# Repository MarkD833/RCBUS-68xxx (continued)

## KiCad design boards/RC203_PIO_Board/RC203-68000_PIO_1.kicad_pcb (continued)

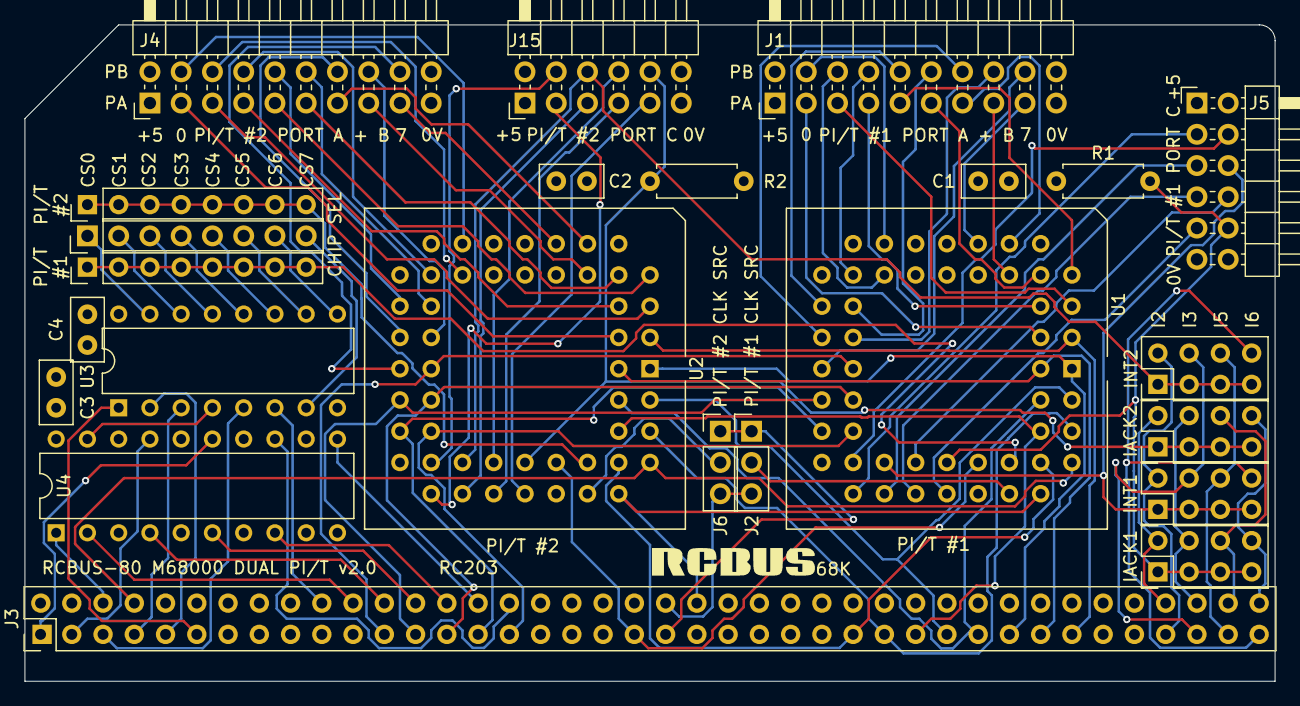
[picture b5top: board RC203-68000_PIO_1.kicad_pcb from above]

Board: 4 copper layers, 101.6 x 53.3 mm, 24 parts (0 on the bottom side), 103 nets.

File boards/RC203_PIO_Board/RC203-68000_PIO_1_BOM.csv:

Reference,Value,Footprint,Qty,Description
"C1,C2,C3,C4",100n,Capacitor_THT:C_Disc_D5.0mm_W2.5mm_P2.50mm,4,Unpolarized ceramic capacitor
"J1,J4,J5",Conn_02x08_Odd_Even,MyLibrary2023:PinHeader_2x08_P2.54mm_Vertical,3,"Generic connector, double row, 02x08, right angle"
"J2,J6",Conn_01x03,Connector_PinHeader_2.54mm:PinHeader_1x03_P2.54mm_Vertical,2,"Generic connector, single row, 01x03"
J3,RCBus_80PIN_68000,MyLibrary2023:RCBus_80p_Medium,1,"Generic connector, double row, 02x40, right angle"
"J7,J12,J13",Conn_01x08,Connector_PinHeader_2.54mm:PinHeader_1x08_P2.54mm_Vertical,3,"Generic connector, single row, 01x08"
"J8,J9,J10,J11",Conn_02x04_Odd_Even,MyLibrary2023:PinHeader_2x04_P2.54mm_Vertical,4,"Generic connector, double row, 02x04"
J14,Conn_02x03_Odd_Even,Connector_PinSocket_2.54mm:PinSocket_2x03_P2.54mm_Vertical,1,"Generic connector, double row, 02x03, right angle"
J15,Conn_01x06,Connector_PinSocket_2.54mm:PinSocket_1x06_P2.54mm_Vertical,1,"Generic connector, single row, 01x06, right angle"
"U1,U2",MC68230,MyLibrary2023:DIP-48_W15.24mm_Socket,2,Parallel Interface / Timer
U3,74LS138,Package_DIP:DIP-16_W7.62mm_Socket,1,Decoder 3 to 8 active low outputs
U4,74LS688,MyLibrary2023:DIP-20_W7.62mm_Socket,1,8-bit magnitude comparator

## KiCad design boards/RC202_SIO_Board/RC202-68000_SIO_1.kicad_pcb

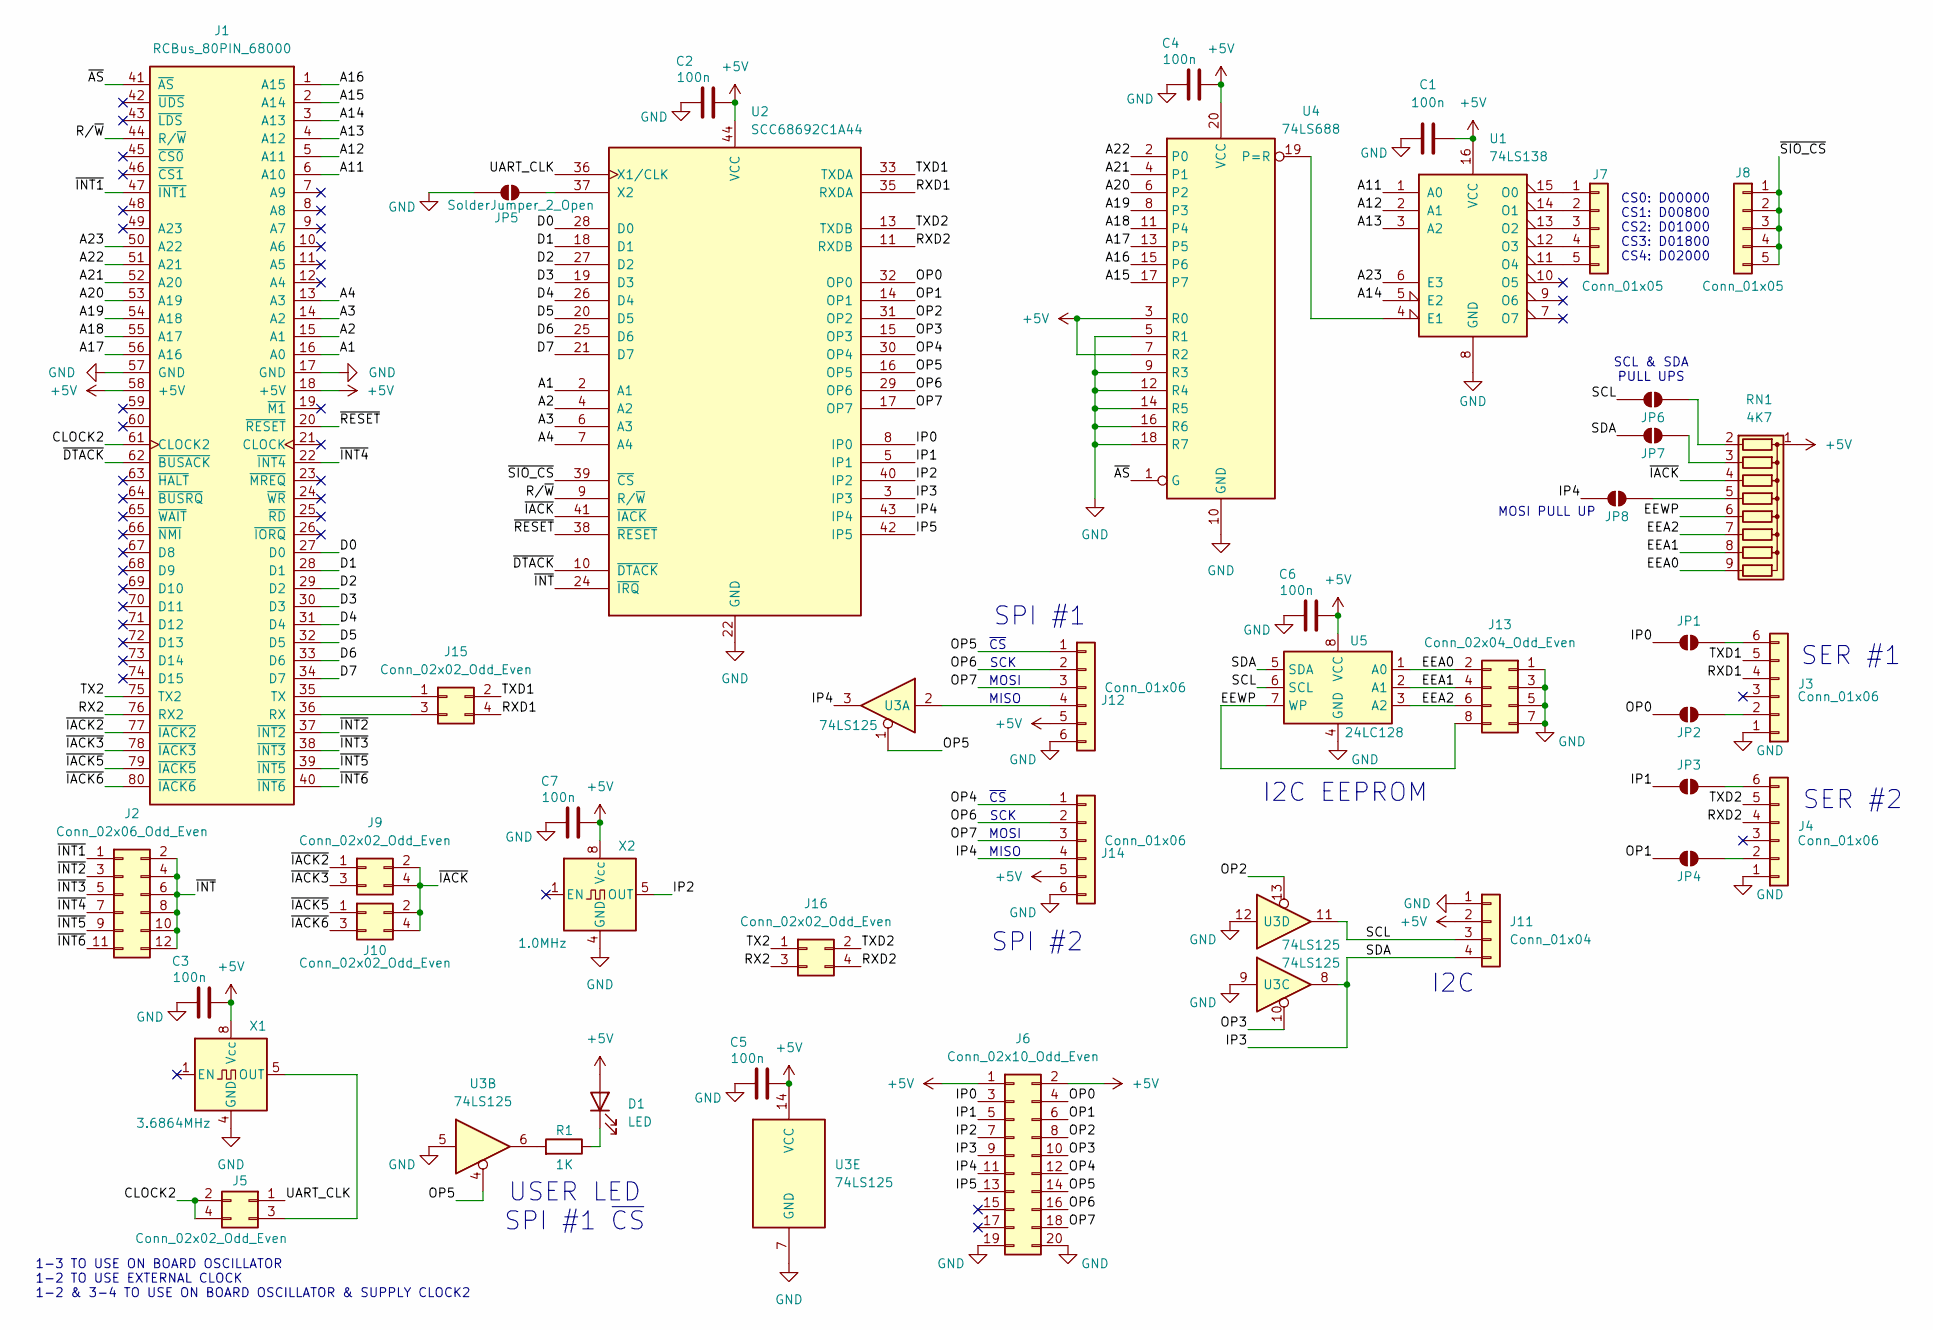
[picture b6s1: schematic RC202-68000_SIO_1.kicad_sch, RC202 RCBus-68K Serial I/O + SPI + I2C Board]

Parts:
C1, C2, C3, C4, C5, C6, C7: 100n; C_Disc_D5.0mm_W2.5mm_P2.50mm
D1: LED; LED_D3.0mm
J1: RCBus_80PIN_68000; RCBus_80p_Medium
J2: Conn_02x06_Odd_Even; PinHeader_2x06_P2.54mm_Vertical
J3, J4, J12, J14: Conn_01x06; PinSocket_1x06_P2.54mm_Horizontal
J5, J9, J10, J15, J16: Conn_02x02_Odd_Even; PinHeader_2x02_P2.54mm_Vertical
J6: Conn_02x10_Odd_Even; PinHeader_2x10_P2.54mm_Horizontal
J7, J8: Conn_01x05; PinHeader_1x05_P2.54mm_Vertical
J11: Conn_01x04; PinHeader_1x04_P2.54mm_Horizontal
J13: Conn_02x04_Odd_Even; PinHeader_2x04_P2.54mm_Vertical
JP1, JP2, JP3, JP4, JP6, JP7, JP8: SolderJumper; SolderJumper-2_P1.3mm_Open_Pad1.0x1.5mm
JP5: SolderJumper_2_Open; SolderJumper-2_P1.3mm_Open_Pad1.0x1.5mm
R1: 1K; R_Axial_DIN0207_L6.3mm_D2.5mm_P7.62mm_Horizontal
RN1: 4K7; R_Array_SIP9
U1: 74LS138; DIP-16_W7.62mm
U2: SCC68692C1A44; PLCC-44_THT-Socket
U3: 74LS125; DIP-14_W7.62mm
U4: 74LS688; DIP-20_W7.62mm
U5: 24LC128; DIP-8_W7.62mm
X1: 3.6864MHz; Oscillator_DIP-8
X2: 1.0MHz; Oscillator_DIP-8

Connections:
+5V: C1.2, C2.2, C3.2, C4.2, C5.2, C6.2, C7.2, D1.2 (A), J1.18 (+5V), J1.58 (+5V), J6.1, J6.2, J11.2, J12.5, J14.5, RN1.1 (common), U1.16 (VCC), U2.44 (VCC), U3.14 (VCC), U4.3 (R0), U4.7 (R2), U4.20 (VCC), U5.8 (VCC), X1.8 (Vcc), X2.8 (Vcc)
/A1: J1.16 (A0), U2.2 (A1)
/A2: J1.15 (A1), U2.4 (A2)
/A3: J1.14 (A2), U2.6 (A3)
/A4: J1.13 (A3), U2.7 (A4)
/A11: J1.6 (A10), U1.1 (A0)
/A12: J1.5 (A11), U1.2 (A1)
/A13: J1.4 (A12), U1.3 (A2)
/A14: J1.3 (A13), U1.5 (E2)
/A15: J1.2 (A14), U4.17 (P7)
/A16: J1.1 (A15), U4.15 (P6)
/A17: J1.56 (A16), U4.13 (P5)
/A18: J1.55 (A17), U4.11 (P4)
/A19: J1.54 (A18), U4.8 (P3)
/A20: J1.53 (A19), U4.6 (P2)
/A21: J1.52 (A20), U4.4 (P1)
/A22: J1.51 (A21), U4.2 (P0)
/A23: J1.50 (A22), U1.6 (E3)
/CLOCK2: J1.61 (CLOCK2), J5.2, J5.4
/D0: J1.27 (D0), U2.28 (D0)
/D1: J1.28 (D1), U2.18 (D1)
/D2: J1.29 (D2), U2.27 (D2)
/D3: J1.30 (D3), U2.19 (D3)
/D4: J1.31 (D4), U2.26 (D4)
/D5: J1.32 (D5), U2.20 (D5)
/D6: J1.33 (D6), U2.25 (D6)
/D7: J1.34 (D7), U2.21 (D7)
/EEA0: J13.2, RN1.9 (R8), U5.1 (A0)
/EEA1: J13.4, RN1.8 (R7), U5.2 (A1)
/EEA2: J13.6, RN1.7 (R6), U5.3 (A2)
/EEWP: J13.8, RN1.6 (R5), U5.7 (WP)
/IP0: J6.3, JP1.1 (A), U2.8 (IP0)
/IP1: J6.5, JP3.1 (A), U2.5 (IP1)
/IP2: J6.7, U2.40 (IP2), X2.5 (OUT)
/IP3: J6.9, J11.4, JP7.1 (A), U2.3 (IP3), U3.8, U5.5 (SDA)
/IP4: J6.11, J14.4, JP8.1 (A), U2.43 (IP4), U3.3
/IP5: J6.13, U2.42 (IP5)
/OP0: J6.4, JP2.1 (A), U2.32 (OP0)
/OP1: J6.6, JP4.1 (A), U2.14 (OP1)
/OP2: J6.8, U2.31 (OP2), U3.13
/OP3: J6.10, U2.15 (OP3), U3.10
/OP4: J6.12, J14.1, U2.30 (OP4)
/OP5: J6.14, J12.1, U2.16 (OP5), U3.1, U3.4
/OP6: J6.16, J12.2, J14.2, U2.29 (OP6)
/OP7: J6.18, J12.3, J14.3, U2.17 (OP7)
/RX2: J1.76 (RX2), J16.3
/RXD1: J3.4, J15.4, U2.35 (RXDA)
/RXD2: J4.4, J16.4, U2.11 (RXDB)
/R/~W: J1.44 (R/~W), U2.9 (R/~W)
/SCL: J11.3, JP6.1 (A), U3.11, U5.6 (SCL)
/TX2: J1.75 (TX2), J16.1
/TXD1: J3.5, J15.2, U2.33 (TXDA)
/TXD2: J4.5, J16.2, U2.13 (TXDB)
/UART_CLK: J5.1, U2.36 (X1/CLK)
/~AS: J1.41 (~AS), U4.1 (G)
/~DTACK: J1.62 (~BUSACK), U2.10 (~DTACK)
/~IACK2: J1.77 (~IACK2), J9.1
/~IACK3: J1.78 (~IACK3), J9.3
/~IACK5: J1.79 (~IACK5), J10.1
/~IACK6: J1.80 (~IACK6), J10.3
/~IACK: J9.2, J9.4, J10.2, J10.4, RN1.4 (R3), U2.41 (~IACK)
/~INT1: J1.47 (~INT1), J2.1
/~INT2: J1.37 (~INT2), J2.3
/~INT3: J1.38 (~INT3), J2.5
/~INT4: J1.22 (~INT4), J2.7
/~INT5: J1.39 (~INT5), J2.9
/~INT6: J1.40 (~INT6), J2.11
/~INT: J2.2, J2.4, J2.6, J2.8, J2.10, J2.12, U2.24 (~IRQ)
/~RESET: J1.20 (~RESET), U2.38 (~RESET)
/~SIO_CS: J8.1, J8.2, J8.3, J8.4, J8.5, U2.39 (~CS)
GND: C1.1, C2.1, C3.1, C4.1, C5.1, C6.1, C7.1, J1.17 (GND), J1.57 (GND), J3.1, J4.1, J6.19, J6.20, J11.1, J12.6, J13.1, J13.3, J13.5, J13.7, J14.6, JP5.2 (B), U1.8 (GND), U2.22 (GND), U3.5, U3.7 (GND), U3.9, U3.12, U4.5 (R1), U4.9 (R3), U4.10 (GND), U4.12 (R4), U4.14 (R5), U4.16 (R6), U4.18 (R7), U5.4 (GND), X1.4 (GND), X2.4 (GND)
unnamed: D1.1 (K), R1.1
unnamed: J1.36 (RX), J15.3
unnamed: J1.35 (TX), J15.1
unnamed: J3.2, JP2.2 (B)
unnamed: J3.6, JP1.2 (B)
unnamed: J4.2, JP4.2 (B)
unnamed: J4.6, JP3.2 (B)
unnamed: J5.3, X1.5 (OUT)
unnamed: J7.1, U1.15 (O0)
unnamed: J7.2, U1.14 (O1)
unnamed: J7.3, U1.13 (O2)
unnamed: J7.4, U1.12 (O3)
unnamed: J7.5, U1.11 (O4)
unnamed: J12.4, U3.2
unnamed: JP5.1 (A), U2.37 (X2)
unnamed: JP6.2 (B), RN1.2 (R1)
unnamed: JP7.2 (B), RN1.3 (R2)
unnamed: JP8.2 (B), RN1.5 (R4)
unnamed: R1.2, U3.6
unnamed: U1.4 (E1), U4.19 (P=R)

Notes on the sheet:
I2C EEPROM
SCK
SCL & SDA PULL UPS
~{CS}
MOSI PULL UP
MISO
MOSI
I2C
CS0: D00000 CS1: D00800 CS2: D01000 CS3: D01800 CS4: D02000
SER #1
SER #2
SPI #1
1-3 TO USE ON BOARD OSCILLATOR 1-2 TO USE EXTERNAL CLOCK 1-2 & 3-4 TO USE ON BOARD OSCILLATOR & SUPPLY CLOCK2
USER LED SPI #1 ~{CS}
SPI #2

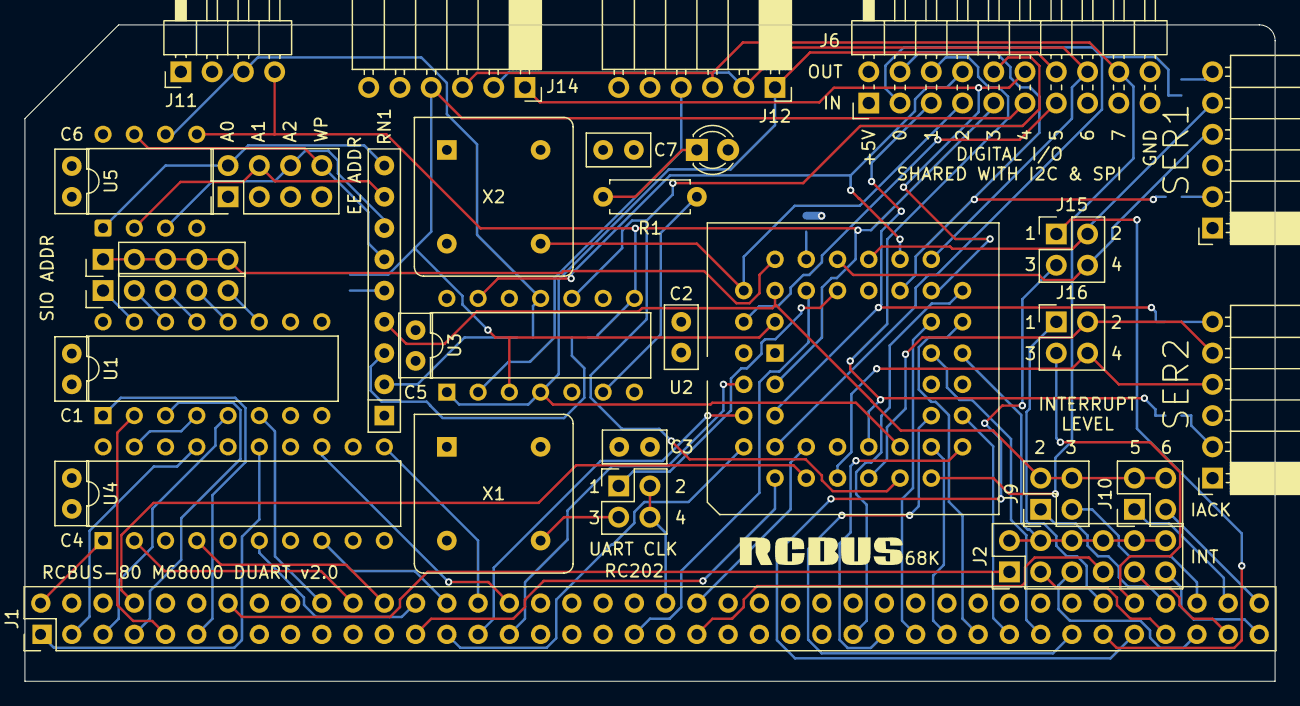
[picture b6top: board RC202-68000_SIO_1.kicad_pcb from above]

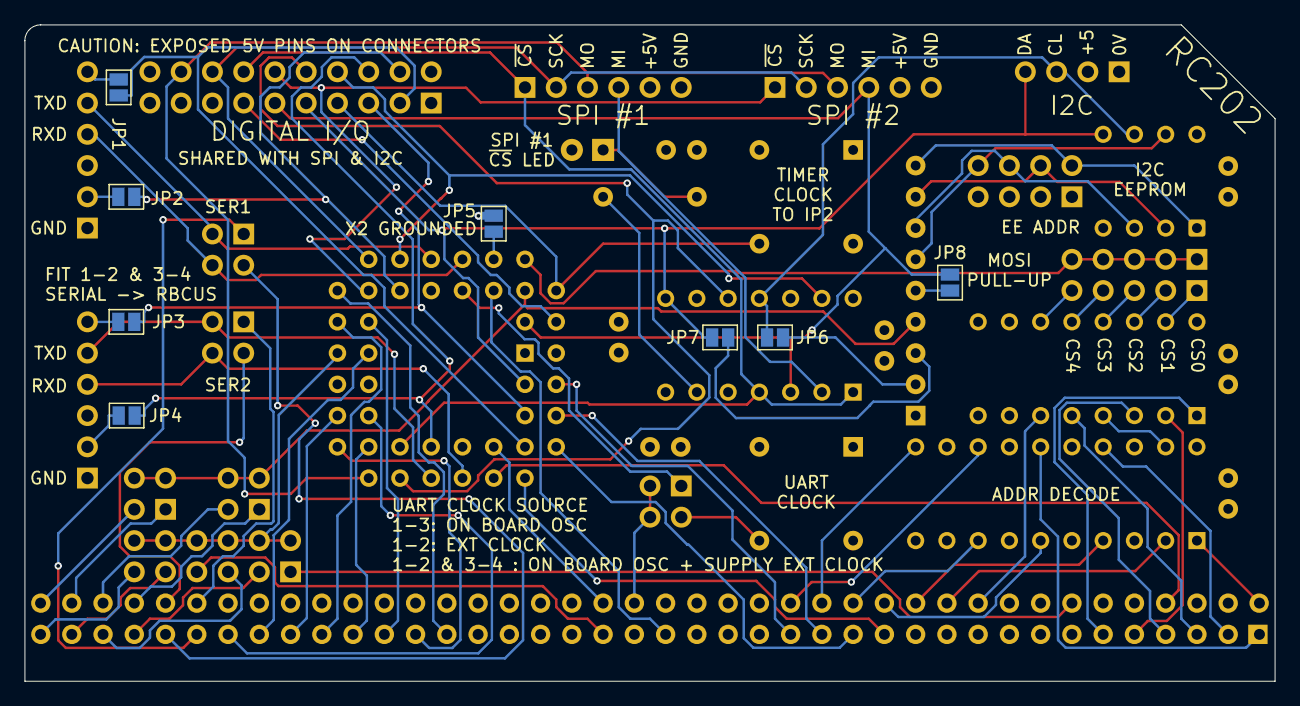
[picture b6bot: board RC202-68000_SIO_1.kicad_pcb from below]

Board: 4 copper layers, 101.6 x 53.3 mm, 41 parts (8 on the bottom side), 91 nets.

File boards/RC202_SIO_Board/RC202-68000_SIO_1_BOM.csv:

Reference,Value,Qty,Description
"C1,C2,C3,C4,C5,C6,C7",100n,7,Unpolarized ceramic capacitor
D1,LED,1,Light emitting diode
J1,RCBus_80PIN_68000,1,"Generic connector, double row, 02x40, right angle"
J2,Conn_02x06_Odd_Even,1,"Generic connector, double row, 02x06"
"J3,J4,J12,J14",Conn_01x06,4,"Generic connector, single row, 01x06, right angle"
"J5,J9,J10,J15,J16",Conn_02x02_Odd_Even,5,"Generic connector, double row, 02x02"
J6,Conn_02x10_Odd_Even,1,"Generic connector, double row, 02x10"
"J7,J8",Conn_01x05,2,"Generic connector, single row, 01x05"
J11,Conn_01x04,1,"Generic connector, single row, 01x04"
J13,Conn_02x04_Odd_Even,1,"Generic connector, double row, 02x04"
"JP1,JP2,JP3,JP4,JP6,JP7,JP8",SolderJumper,7,"Solder Jumper, 2-pole, open"
R1,1K,1,Resistor
RN1,4K7,1,"8 resistor network, star topology, bussed resistors, small symbol"
U1,74LS138,1,Decoder 3 to 8 active low outputs
U2,SCC68692C1A44,1,DUART + 8 Outputs & 6 Inputs
U3,74LS125,1,Quad buffer 3-State outputs
U4,74LS688,1,8-bit magnitude comparator
U5,24LC128,1,"I2C Serial EEPROM, 128Kb, DIP-8"
X1,3.6864MHz,1,"Crystal Clock Oscillator, DIP8-style metal package"
X2,1.0MHz,1,"Crystal Clock Oscillator, DIP8-style metal package"

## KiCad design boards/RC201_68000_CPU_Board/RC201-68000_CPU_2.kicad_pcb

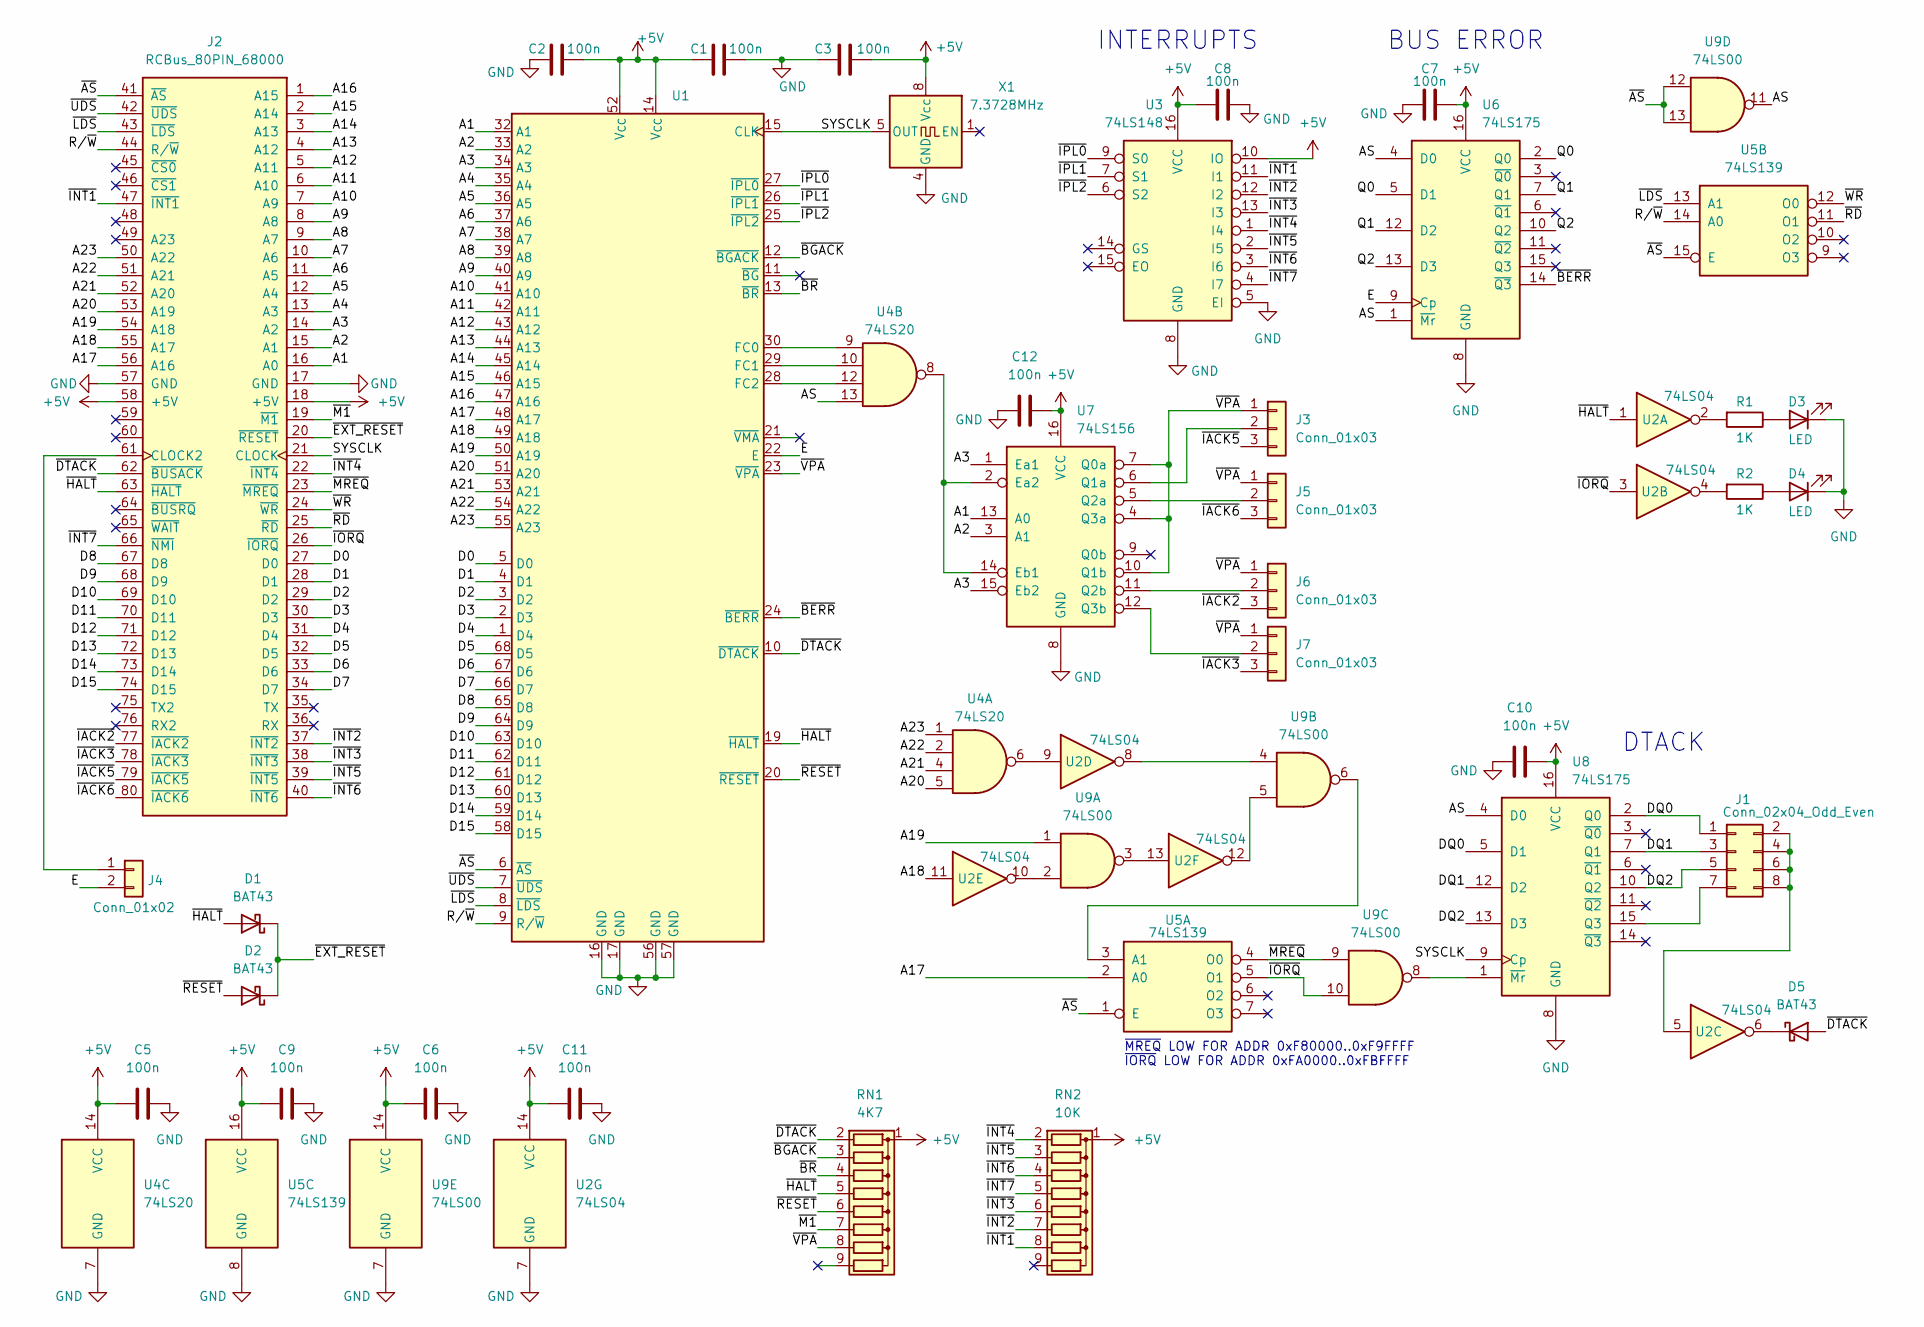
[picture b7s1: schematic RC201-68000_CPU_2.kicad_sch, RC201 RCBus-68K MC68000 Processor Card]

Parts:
C1, C2, C3, C5, C6, C7, C8, C9, C10, C11, C12: 100n; C_Disc_D5.0mm_W2.5mm_P2.50mm
D1, D2, D5: BAT43; D_DO-35_SOD27_P7.62mm_Horizontal
D3, D4: LED; LED_D3.0mm
J1: Conn_02x04_Odd_Even; PinHeader_2x04_P2.54mm_Vertical
J2: RCBus_80PIN_68000; RCBus_80p_Medium
J3, J5, J6, J7: Conn_01x03; PinHeader_1x03_P2.54mm_Vertical
J4: Conn_01x02; PinHeader_1x02_P2.54mm_Vertical
R1, R2: 1K; R_Axial_DIN0207_L6.3mm_D2.5mm_P7.62mm_Horizontal
RN1: 4K7; R_Array_SIP9
RN2: 10K; R_Array_SIP9
U1: PLCC-68_THT-Socket
U2: 74LS04; DIP-14_W7.62mm
U3: 74LS148; DIP-16_W7.62mm
U4: 74LS20; DIP-14_W7.62mm
U5: 74LS139; DIP-16_W7.62mm
U6, U8: 74LS175; DIP-16_W7.62mm
U7: 74LS156; DIP-16_W7.62mm
U9: 74LS00; DIP-14_W7.62mm
X1: 7.3728MHz; Oscillator_DIP-8

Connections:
+5V: C1.1, C2.2, C3.2, C5.1, C6.1, C7.2, C8.1, C9.1, C10.2, C11.1, C12.2, J2.18 (+5V), J2.58 (+5V), RN1.1 (common), RN2.1 (common), U1.14 (V_{CC}), U1.52 (V_{CC}), U2.14 (VCC), U3.10 (IO), U3.16 (VCC), U4.14 (VCC), U5.16 (VCC), U6.16 (VCC), U7.16 (VCC), U8.16 (VCC), U9.14 (VCC), X1.8 (Vcc)
/A1: J2.16 (A0), U1.32 (A1), U7.13 (A0)
/A2: J2.15 (A1), U1.33 (A2), U7.3 (A1)
/A3: J2.14 (A2), U1.34 (A3), U7.1 (Ea1), U7.15 (Eb2)
/A4: J2.13 (A3), U1.35 (A4)
/A5: J2.12 (A4), U1.36 (A5)
/A6: J2.11 (A5), U1.37 (A6)
/A7: J2.10 (A6), U1.38 (A7)
/A8: J2.9 (A7), U1.39 (A8)
/A9: J2.8 (A8), U1.40 (A9)
/A10: J2.7 (A9), U1.41 (A10)
/A11: J2.6 (A10), U1.42 (A11)
/A12: J2.5 (A11), U1.43 (A12)
/A13: J2.4 (A12), U1.44 (A13)
/A14: J2.3 (A13), U1.45 (A14)
/A15: J2.2 (A14), U1.46 (A15)
/A16: J2.1 (A15), U1.47 (A16)
/A17: J2.56 (A16), U1.48 (A17), U5.2 (A0)
/A18: J2.55 (A17), U1.49 (A18), U2.11
/A19: J2.54 (A18), U1.50 (A19), U9.1
/A20: J2.53 (A19), U1.51 (A20), U4.5
/A21: J2.52 (A20), U1.53 (A21), U4.4
/A22: J2.51 (A21), U1.54 (A22), U4.2
/A23: J2.50 (A22), U1.55 (A23), U4.1
/AS: U4.13, U6.1 (~Mr), U6.4 (D0), U8.4 (D0), U9.11
/D0: J2.27 (D0), U1.5 (D0)
/D1: J2.28 (D1), U1.4 (D1)
/D2: J2.29 (D2), U1.3 (D2)
/D3: J2.30 (D3), U1.2 (D3)
/D4: J2.31 (D4), U1.1 (D4)
/D5: J2.32 (D5), U1.68 (D5)
/D6: J2.33 (D6), U1.67 (D6)
/D7: J2.34 (D7), U1.66 (D7)
/D8: J2.67 (D8), U1.65 (D8)
/D9: J2.68 (D9), U1.64 (D9)
/D10: J2.69 (D10), U1.63 (D10)
/D11: J2.70 (D11), U1.62 (D11)
/D12: J2.71 (D12), U1.61 (D12)
/D13: J2.72 (D13), U1.60 (D13)
/D14: J2.73 (D14), U1.59 (D14)
/D15: J2.74 (D15), U1.58 (D15)
/DQ0: J1.1, U8.2 (Q0), U8.5 (D1)
/DQ1: J1.3, U8.7 (Q1), U8.12 (D2)
/DQ2: J1.5, U8.10 (Q2), U8.13 (D3)
/E: J4.2, U1.22 (E), U6.9 (Cp)
/Q0: U6.2 (Q0), U6.5 (D1)
/Q1: U6.7 (Q1), U6.12 (D2)
/Q2: U6.10 (Q2), U6.13 (D3)
/R/~W: J2.44 (R/~W), U1.9 (R/~W), U5.14 (A0)
/SYSCLK: J2.21 (CLOCK), U1.15 (CLK), U8.9 (Cp), X1.5 (OUT)
/~AS: J2.41 (~AS), U1.6 (~AS), U5.1 (E), U5.15 (E), U9.12, U9.13
/~BERR: U1.24 (~BERR), U6.14 (~Q3)
/~BGACK: RN1.3 (R2), U1.12 (~BGACK)
/~BR: RN1.4 (R3), U1.13 (~BR)
/~DTACK: D5.2 (A), J2.62 (~BUSACK), RN1.2 (R1), U1.10 (~DTACK)
/~EXT_RESET: D1.1 (K), D2.1 (K), J2.20 (~RESET)
/~HALT: D1.2 (A), J2.63 (~HALT), RN1.5 (R4), U1.19 (~HALT), U2.1
/~IACK2: J2.77 (~IACK2), J6.3
/~IACK3: J2.78 (~IACK3), J7.3
/~IACK5: J2.79 (~IACK5), J3.3
/~IACK6: J2.80 (~IACK6), J5.3
/~INT1: J2.47 (~INT1), RN2.8 (R7), U3.11 (I1)
/~INT2: J2.37 (~INT2), RN2.7 (R6), U3.12 (I2)
/~INT3: J2.38 (~INT3), RN2.6 (R5), U3.13 (I3)
/~INT4: J2.22 (~INT4), RN2.2 (R1), U3.1 (I4)
/~INT5: J2.39 (~INT5), RN2.3 (R2), U3.2 (I5)
/~INT6: J2.40 (~INT6), RN2.4 (R3), U3.3 (I6)
/~INT7: J2.66 (~NMI), RN2.5 (R4), U3.4 (I7)
/~IORQ: J2.26 (~IORQ), U2.3, U5.5 (O1), U9.10
/~IPL0: U1.27 (~IPL0), U3.9 (S0)
/~IPL1: U1.26 (~IPL1), U3.7 (S1)
/~IPL2: U1.25 (~IPL2), U3.6 (S2)
/~LDS: J2.43 (~LDS), U1.8 (~LDS), U5.13 (A1)
/~M1: J2.19 (~M1), RN1.7 (R6)
/~MREQ: J2.23 (~MREQ), U5.4 (O0), U9.9
/~RD: J2.25 (~RD), U5.11 (O1)
/~RESET: D2.2 (A), RN1.6 (R5), U1.20 (~RESET)
/~UDS: J2.42 (~UDS), U1.7 (~UDS)
/~VPA: J3.1, J5.1, J6.1, J7.1, RN1.8 (R7), U1.23 (~VPA), U7.4 (Q3a), U7.7 (Q0a), U7.10 (Q1b)
/~WR: J2.24 (~WR), U5.12 (O0)
GND: C1.2, C2.1, C3.1, C5.2, C6.2, C7.1, C8.2, C9.2, C10.1, C11.2, C12.1, D3.1 (K), D4.1 (K), J2.17 (GND), J2.57 (GND), U1.16 (GND), U1.17 (GND), U1.56 (GND), U1.57 (GND), U2.7 (GND), U3.5 (EI), U3.8 (GND), U4.7 (GND), U5.8 (GND), U6.8 (GND), U7.8 (GND), U8.8 (GND), U9.7 (GND), X1.4 (GND)
unnamed: D3.2 (A), R1.1
unnamed: D4.2 (A), R2.1
unnamed: D5.1 (K), U2.6
unnamed: J1.2, J1.4, J1.6, J1.8, U2.5
unnamed: J1.7, U8.15 (Q3)
unnamed: J2.61 (CLOCK2), J4.1
unnamed: J3.2, U7.6 (Q1a)
unnamed: J5.2, U7.5 (Q2a)
unnamed: J6.2, U7.11 (Q2b)
unnamed: J7.2, U7.12 (Q3b)
unnamed: R1.2, U2.2
unnamed: R2.2, U2.4
unnamed: U1.30 (FC0), U4.9
unnamed: U1.29 (FC1), U4.10
unnamed: U1.28 (FC2), U4.12
unnamed: U2.8, U9.4
unnamed: U2.9, U4.6
unnamed: U2.10, U9.2
unnamed: U2.12, U9.5
unnamed: U2.13, U9.3
unnamed: U5.3 (A1), U9.6
unnamed: U4.8, U7.2 (Ea2), U7.14 (Eb1)
unnamed: U8.1 (~Mr), U9.8

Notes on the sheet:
INTERRUPTS
DTACK
~{MREQ} LOW FOR ADDR 0xF80000..0xF9FFFF ~{IORQ} LOW FOR ADDR 0xFA0000..0xFBFFFF
BUS ERROR

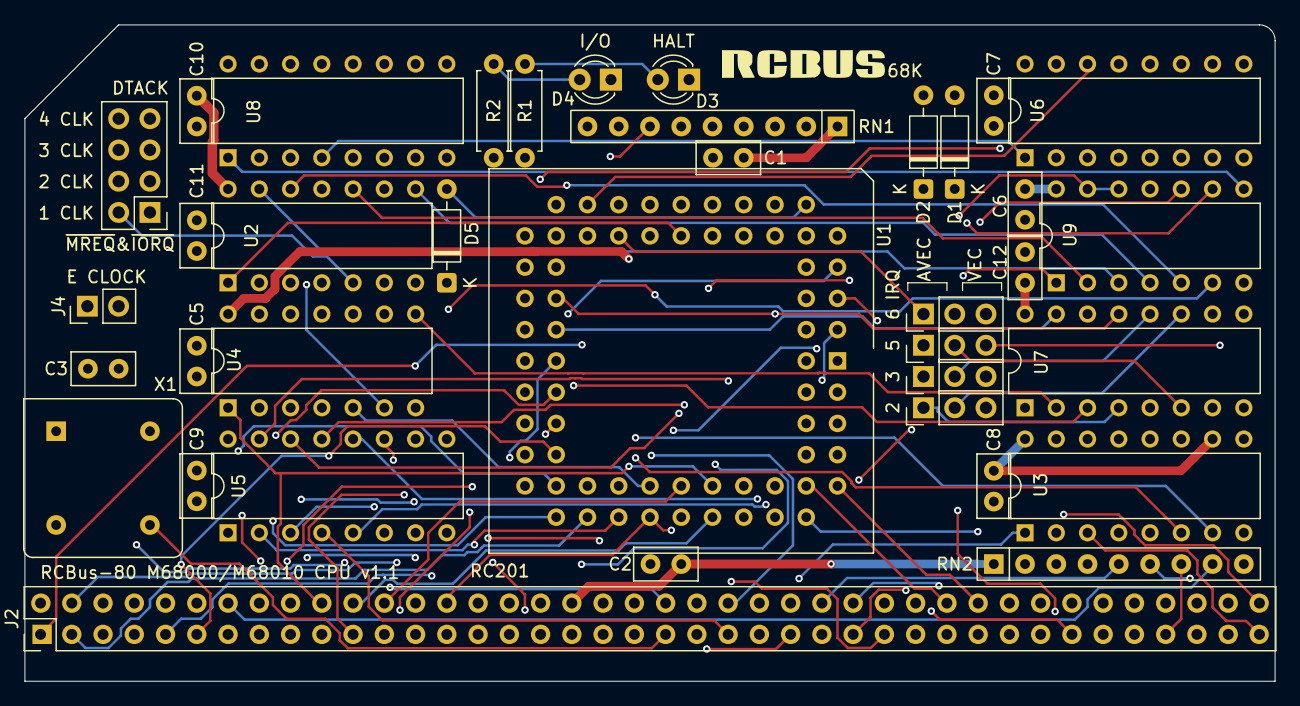
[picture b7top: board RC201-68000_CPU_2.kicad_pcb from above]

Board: 4 copper layers, 101.6 x 53.3 mm, 37 parts (0 on the bottom side), 104 nets.

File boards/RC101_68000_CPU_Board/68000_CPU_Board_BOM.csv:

"Reference","Value","Footprint","Qty","Description"
"C1,C2,C3,C5,C6,C7,C8,C9,C10,C11","100n","Capacitor_THT:C_Disc_D5.0mm_W2.5mm_P2.50mm","10","Unpolarized ceramic capacitor"
"D1,D2","BAT43","Diode_THT:D_DO-35_SOD27_P7.62mm_Horizontal","2","30V 0.2A Small Signal Schottky Diode, DO-35"
"D3,D4,D5","LED","LED_THT:LED_D3.0mm","3","Light emitting diode"
"J1","Conn_02x04_Odd_Even","Connector_PinHeader_2.54mm:PinHeader_2x04_P2.54mm_Vertical","1","Generic connector, double row, 02x04"
"J2","RCBus_80PIN_68000","MyLibrary2023:RCBus_80p_Medium","1","Generic connector, double row, 02x40, right angle"
"J4","Conn_01x02","Connector_PinHeader_2.54mm:PinHeader_1x02_P2.54mm_Vertical","1","Generic connector, single row, 01x02"
"R1,R2,R3","1K","Resistor_THT:R_Axial_DIN0207_L6.3mm_D2.5mm_P7.62mm_Horizontal","3","Resistor"
"RN1","4K7","Resistor_THT:R_Array_SIP9","1","8 resistor network, star topology, bussed resistors, small symbol"
"RN2","10K","Resistor_THT:R_Array_SIP9","1","8 resistor network, star topology, bussed resistors, small symbol"
"U1","MC68000FN","Package_LCC:PLCC-68_THT-Socket","1","Microprocessor, 16-bit bus"
"U2","74LS125","MyLibrary2023:DIP-14_W7.62mm_Socket","1","Quad buffer 3-State outputs"
"U3","74LS148","Package_DIP:DIP-16_W7.62mm_Socket","1","8 line to 3 line priority encoder"
"U4","74LS10","Package_DIP:DIP-14_W7.62mm_Socket","1","Triple 3-input NAND"
"U5","74LS139","Package_DIP:DIP-16_W7.62mm_Socket","1","Dual Decoder 1 of 4, Active low outputs"
"U6,U8","74LS175","Package_DIP:DIP-16_W7.62mm_Socket","2","4-bit D Flip-Flop, reset"
"U9","74LS00","Package_DIP:DIP-14_W7.62mm_Socket","1","quad 2-input NAND gate"
"X1","7.3728MHz","Oscillator:Oscillator_DIP-8","1","Crystal Clock Oscillator, DIP8-style metal package"
